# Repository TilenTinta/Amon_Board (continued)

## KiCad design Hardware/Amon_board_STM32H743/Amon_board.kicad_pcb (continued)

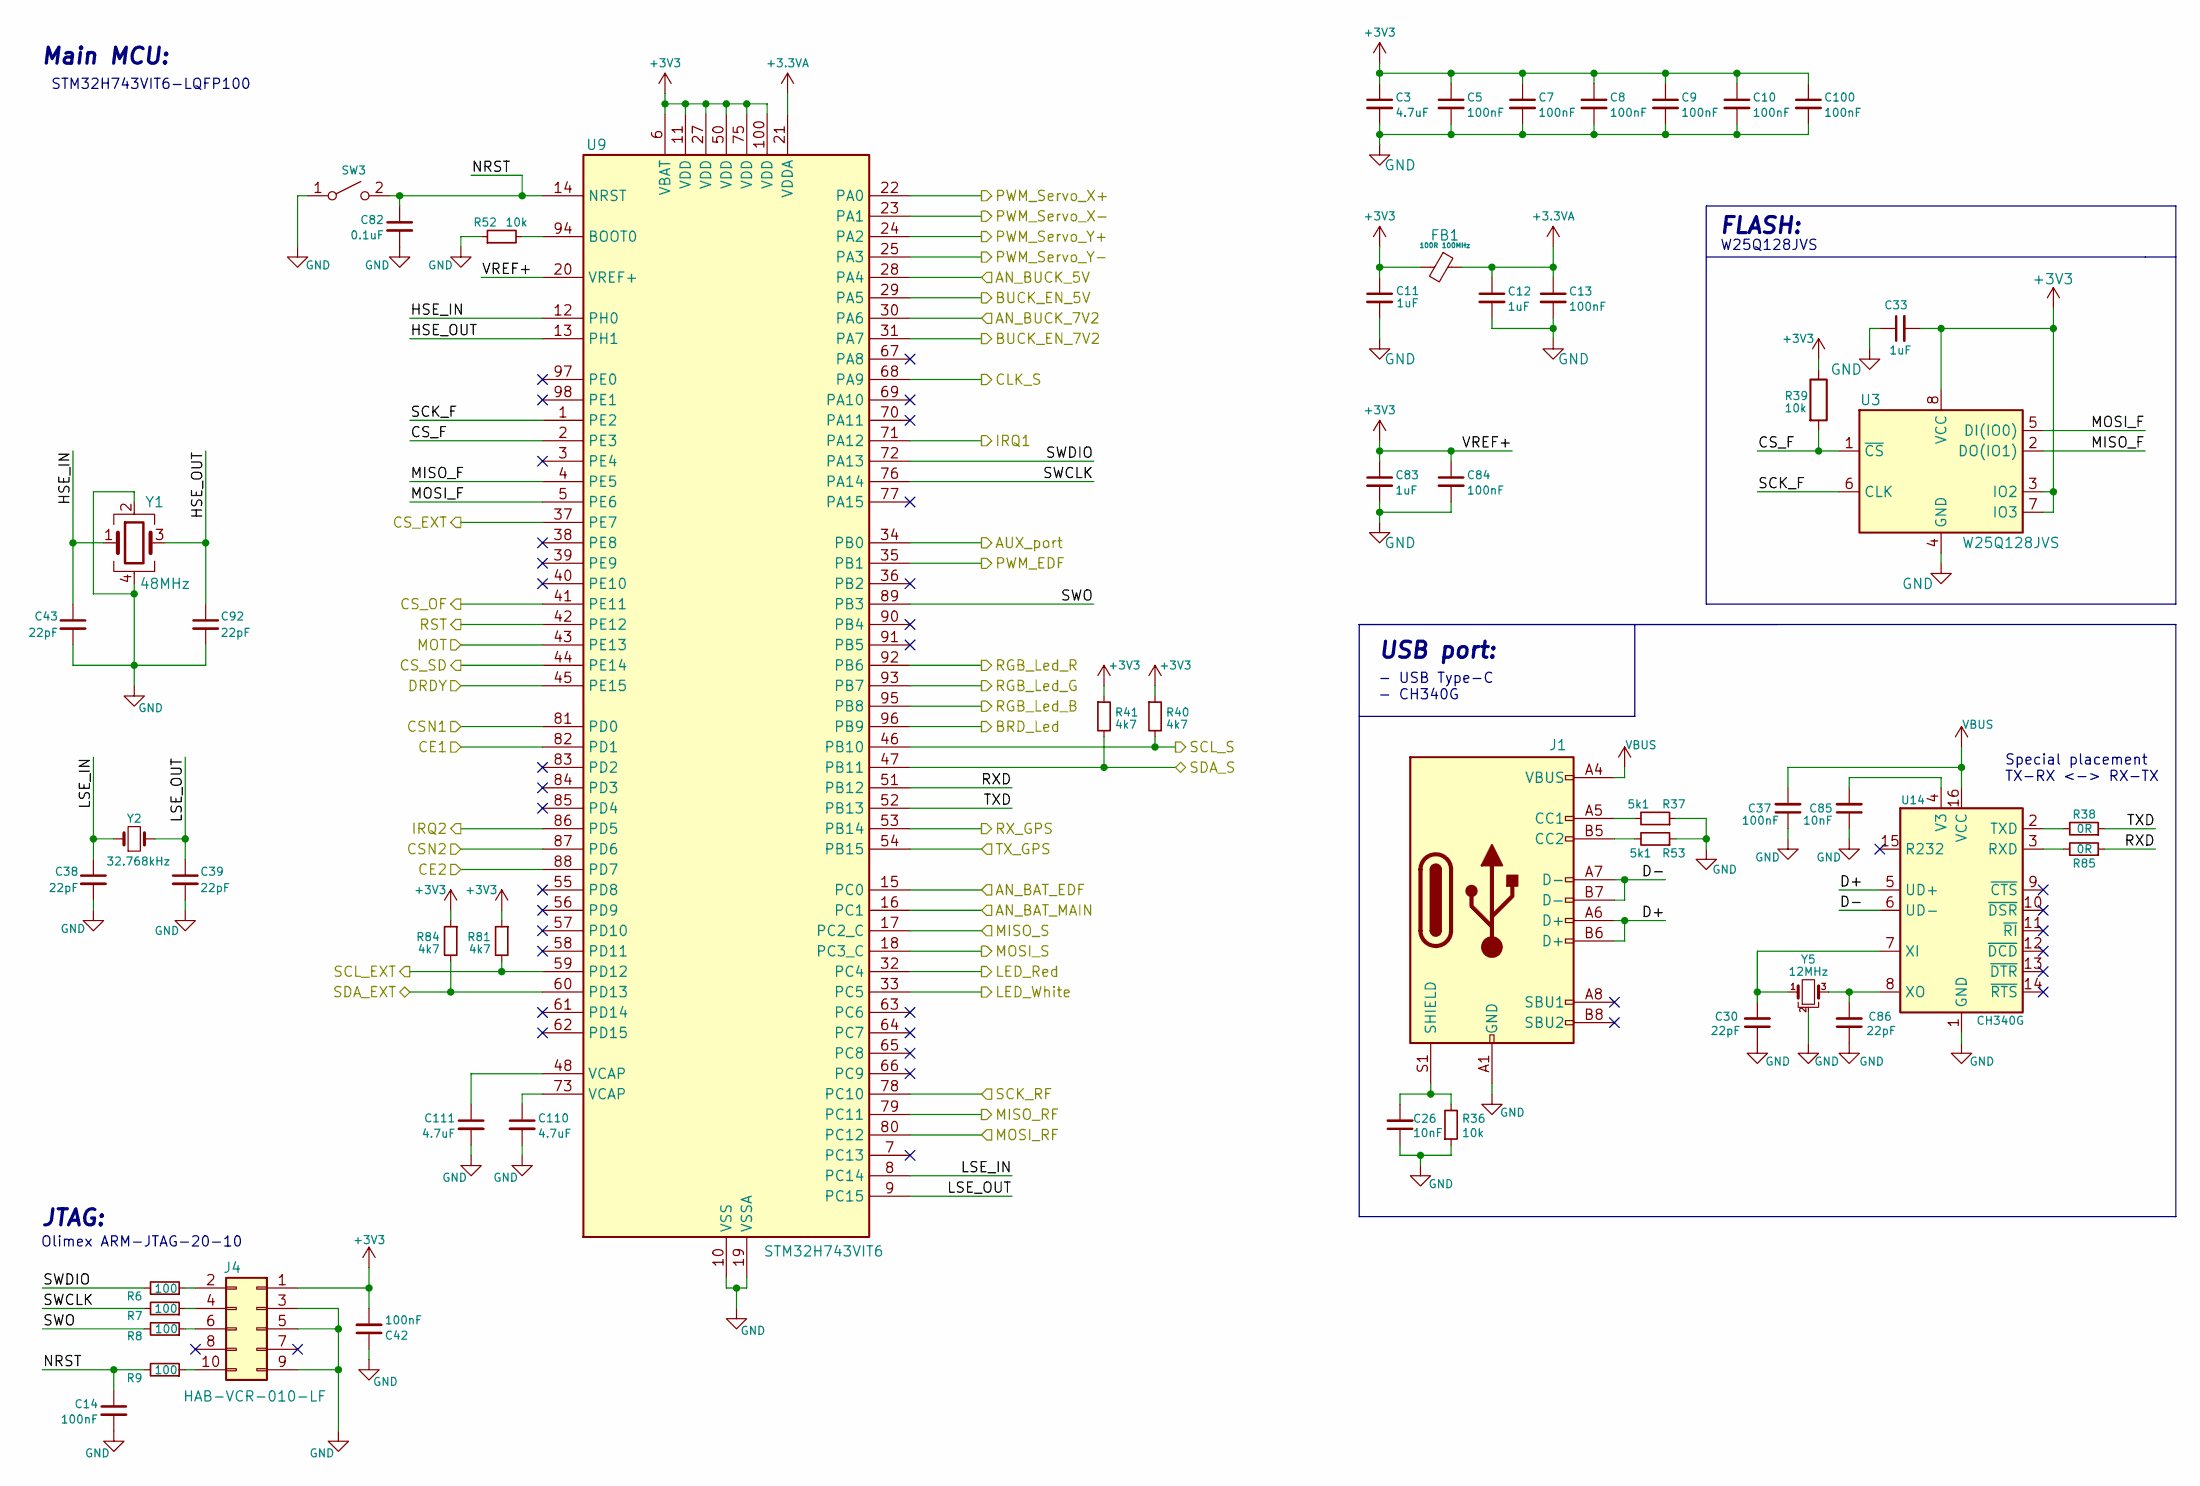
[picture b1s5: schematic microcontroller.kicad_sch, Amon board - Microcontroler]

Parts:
C3, C110, C111: 4.7uF; C_0603_1608Metric
C5, C7, C8, C9, C10, C13, C14, C37, C42, C84, C100: 100nF; C_0603_1608Metric
C11, C12, C33, C83: 1uF; C_0603_1608Metric
C26, C85: 10nF; C_0603_1608Metric
C30, C38, C39, C43, C86, C92: 22pF; C_0402_1005Metric
C82: 0.1uF; C_0603_1608Metric
FB1: 100R 100MHz; L_1206_3216Metric_Pad1.22x1.90mm_HandSolder
J1: USB_C_Receptacle_USB2.0; USB_C_Receptacle_XKB_U262-16XN-4BVC11
J4: HAB-VCR-010-LF; PinHeader_2x05_P1.27mm_Vertical_SMD
R6, R7, R8, R9: 100; R_0603_1608Metric
R36, R39, R52: 10k; R_0603_1608Metric
R37, R53: 5k1; R_0603_1608Metric
R38, R85: 0R; R_0603_1608Metric
R40, R41, R81, R84: 4k7; R_0603_1608Metric
SW3: SW_SPST; SW_Push_1P1T_NO_CK_KMR2
U3: W25Q128JVS; SOIC-8_5.23x5.23mm_P1.27mm
U9: STM32H743VIT6; LQFP-100_14x14mm_P0.5mm
U14: CH340G; SOIC-16_3.9x9.9mm_P1.27mm
Y1: 48MHz; Crystal_SMD_3225-4Pin_3.2x2.5mm
Y2: 32.768kHz; Crystal_SMD_3215-2Pin_3.2x1.5mm
Y5: 12MHz; Resonator_SMD_Murata_CSTxExxV-3Pin_3.0x1.1mm

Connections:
+3.3VA: C12.1, C13.1, FB1.1, U9.21 (VDDA)
/Devices/BRD_Led: U9.96 (PB9); also elsewhere on the board
/Devices/CLK_S: U9.68 (PA9); also elsewhere on the board
/Devices/CS_OF: U9.41 (PE11); also elsewhere on the board
/Devices/CS_SD: U9.44 (PE14); also elsewhere on the board
/Devices/DRDY: U9.45 (PE15); also elsewhere on the board
/Devices/MISO_S: U9.17 (PC2_C); also elsewhere on the board
/Devices/MOSI_S: U9.18 (PC3_C); also elsewhere on the board
/Devices/RGB_Led_B: U9.95 (PB8); also elsewhere on the board
/Devices/RGB_Led_G: U9.93 (PB7); also elsewhere on the board
/Devices/RGB_Led_R: U9.92 (PB6); also elsewhere on the board
/Microcontroller/AN_BAT_EDF: U9.15 (PC0); also elsewhere on the board
/Microcontroller/AN_BAT_MAIN: U9.16 (PC1); also elsewhere on the board
/Microcontroller/AN_BUCK_5V: U9.28 (PA4); also elsewhere on the board
/Microcontroller/AN_BUCK_7V2: U9.30 (PA6); also elsewhere on the board
/Microcontroller/AUX_port: U9.34 (PB0); also elsewhere on the board
/Microcontroller/BUCK_EN_5V: U9.29 (PA5); also elsewhere on the board
/Microcontroller/BUCK_EN_7V2: U9.31 (PA7); also elsewhere on the board
/Microcontroller/CSN1: U9.81 (PD0); also elsewhere on the board
/Microcontroller/CSN2: U9.87 (PD6); also elsewhere on the board
/Microcontroller/CS_EXT: U9.37 (PE7); also elsewhere on the board
/Microcontroller/CS_F: R39.2, U3.1 (~CS), U9.2 (PE3)
/Microcontroller/D+: J1.A6 (D+), J1.B6 (D+), U14.5 (UD+)
/Microcontroller/D-: J1.A7 (D-), J1.B7 (D-), U14.6 (UD-)
/Microcontroller/HSE_IN: C43.1, U9.12 (PH0), Y1.1
/Microcontroller/HSE_OUT: C92.1, U9.13 (PH1), Y1.3
/Microcontroller/IRQ1: U9.71 (PA12); also elsewhere on the board
/Microcontroller/IRQ2: U9.86 (PD5); also elsewhere on the board
/Microcontroller/LED_Red: U9.32 (PC4); also elsewhere on the board
/Microcontroller/LED_White: U9.33 (PC5); also elsewhere on the board
/Microcontroller/LSE_IN: C38.1, U9.8 (PC14), Y2.1
/Microcontroller/LSE_OUT: C39.1, U9.9 (PC15), Y2.2
/Microcontroller/MISO_F: U3.2 (DO(IO1)), U9.4 (PE5)
/Microcontroller/MISO_RF: U9.79 (PC11); also elsewhere on the board
/Microcontroller/MOSI_F: U3.5 (DI(IO0)), U9.5 (PE6)
/Microcontroller/MOSI_RF: U9.80 (PC12); also elsewhere on the board
/Microcontroller/NRST: C14.1, C82.1, R9.2, SW3.2 (B), U9.14 (NRST)
/Microcontroller/PWM_EDF: U9.35 (PB1); also elsewhere on the board
/Microcontroller/PWM_Servo_X+: U9.22 (PA0); also elsewhere on the board
/Microcontroller/PWM_Servo_X-: U9.23 (PA1); also elsewhere on the board
/Microcontroller/PWM_Servo_Y+: U9.24 (PA2); also elsewhere on the board
/Microcontroller/PWM_Servo_Y-: U9.25 (PA3); also elsewhere on the board
/Microcontroller/RXD: R85.1, U9.51 (PB12)
/Microcontroller/RX_GPS: U9.53 (PB14); also elsewhere on the board
/Microcontroller/SCK_F: U3.6 (CLK), U9.1 (PE2)
/Microcontroller/SCK_RF: U9.78 (PC10); also elsewhere on the board
/Microcontroller/SCL_EXT: R81.2, U9.59 (PD12); also elsewhere on the board
/Microcontroller/SDA_EXT: R84.2, U9.60 (PD13); also elsewhere on the board
/Microcontroller/SWCLK: R7.2, U9.76 (PA14)
/Microcontroller/SWDIO: R6.2, U9.72 (PA13)
/Microcontroller/SWO: R8.2, U9.89 (PB3)
/Microcontroller/TXD: R38.1, U9.52 (PB13)
/Microcontroller/TX_GPS: U9.54 (PB15); also elsewhere on the board
/RF/CE1: U9.82 (PD1); also elsewhere on the board
/RF/CE2: U9.88 (PD7); also elsewhere on the board
unnamed: C110.1, U9.73 (VCAP)
unnamed: C111.1, U9.48 (VCAP)
unnamed: J1.A5 (CC1), R37.2
unnamed: J1.B5 (CC2), R53.2
unnamed: C26.2, J1.S1 (SHIELD), R36.2
unnamed: J4.2, R6.1
unnamed: J4.4, R7.1
unnamed: J4.6, R8.1
unnamed: J4.10, R9.1
unnamed: R52.2, U9.94 (BOOT0)
unnamed: R85.2, U14.3 (RXD)
unnamed: R38.2, U14.2 (TXD)
unnamed: C85.2, U14.4 (V3)
unnamed: C30.2, U14.7 (XI), Y5.1
unnamed: C86.2, U14.8 (XO), Y5.3
VBUS: C37.2, J1.A4 (VBUS), J1.A9 (VBUS), J1.B4 (VBUS), J1.B9 (VBUS), U14.16 (VCC)

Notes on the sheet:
- USB Type-C - CH340G
USB port:
Main MCU:
JTAG:
Olimex ARM-JTAG-20-10
W25Q128JVS
STM32H743VIT6-LQFP100
FLASH:
Special placement TX-RX <-> RX-TX

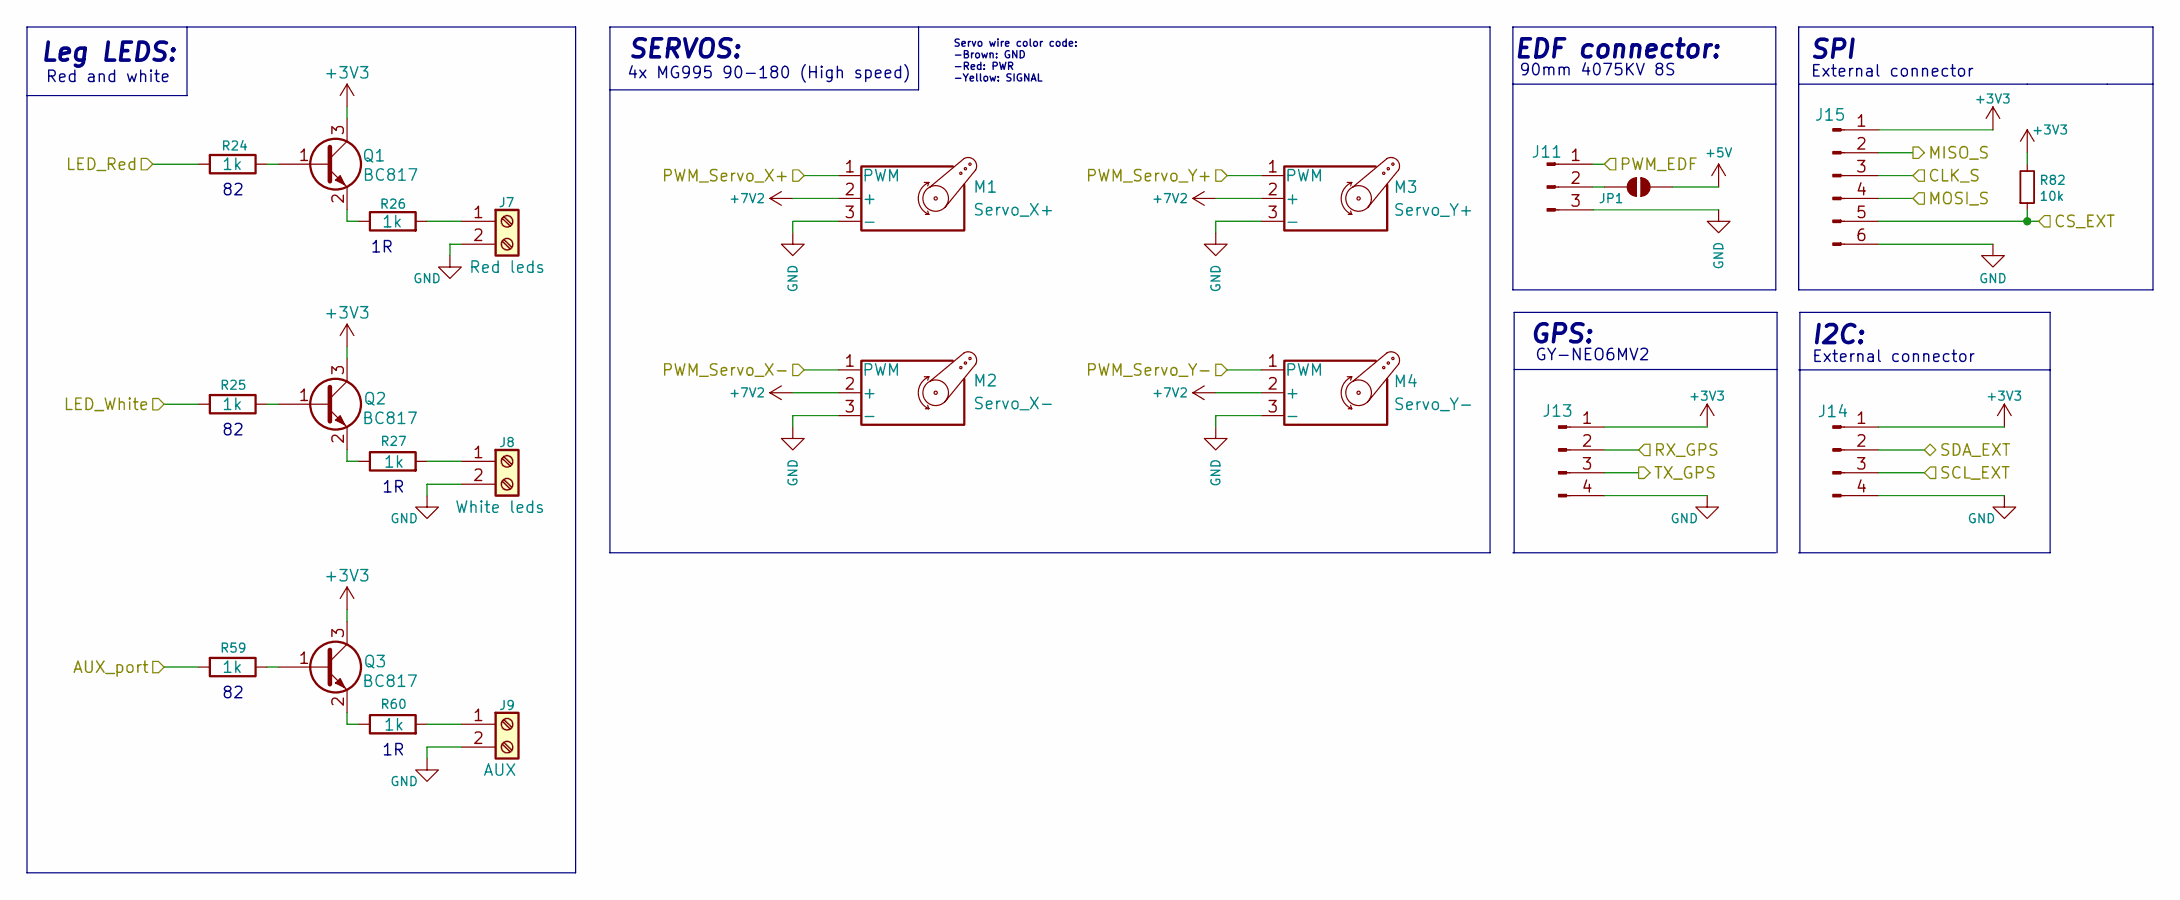
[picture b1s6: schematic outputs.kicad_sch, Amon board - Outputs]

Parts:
J7: Red leds; TerminalBlock_MetzConnect_Type059_RT06302HBWC_1x02_P3.50mm_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
J8: White leds; TerminalBlock_MetzConnect_Type059_RT06302HBWC_1x02_P3.50mm_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
J9: AUX; TerminalBlock_MetzConnect_Type059_RT06302HBWC_1x02_P3.50mm_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
J11: Conn_01x03_Male; PinHeader_1x03_P2.54mm_Vertical
J13: Conn_01x04_Male; JST_XH_S4B-XH-A_1x04_P2.50mm_Horizontal
J14: Conn_01x04_Male; PinHeader_1x04_P2.54mm_Vertical
J15: Conn_01x06_Male; PinHeader_1x06_P2.54mm_Vertical
JP1: SolderJumper_2_Open; SolderJumper-2_P1.3mm_Open_RoundedPad1.0x1.5mm
M1: Servo_X+; PinHeader_1x03_P2.54mm_Vertical
M2: Servo_X-; PinHeader_1x03_P2.54mm_Vertical
M3: Servo_Y+; PinHeader_1x03_P2.54mm_Vertical
M4: Servo_Y-; PinHeader_1x03_P2.54mm_Vertical
Q1, Q2, Q3: BC817; SOT-23
R24, R25, R26, R27, R59, R60: 1k; R_0603_1608Metric
R82: 10k; R_0603_1608Metric

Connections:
+5V: JP1.2 (B); also elsewhere on the board
+7V2: M1.2 (+), M2.2 (+), M3.2 (+), M4.2 (+); also elsewhere on the board
/Devices/CLK_S: J15.3; also elsewhere on the board
/Devices/MISO_S: J15.2; also elsewhere on the board
/Devices/MOSI_S: J15.4; also elsewhere on the board
/Microcontroller/AUX_port: R59.2; also elsewhere on the board
/Microcontroller/CS_EXT: J15.5, R82.1; also elsewhere on the board
/Microcontroller/LED_Red: R24.2; also elsewhere on the board
/Microcontroller/LED_White: R25.2; also elsewhere on the board
/Microcontroller/PWM_EDF: J11.1; also elsewhere on the board
/Microcontroller/PWM_Servo_X+: M1.1 (PWM); also elsewhere on the board
/Microcontroller/PWM_Servo_X-: M2.1 (PWM); also elsewhere on the board
/Microcontroller/PWM_Servo_Y+: M3.1 (PWM); also elsewhere on the board
/Microcontroller/PWM_Servo_Y-: M4.1 (PWM); also elsewhere on the board
/Microcontroller/RX_GPS: J13.2; also elsewhere on the board
/Microcontroller/SCL_EXT: J14.3; also elsewhere on the board
/Microcontroller/SDA_EXT: J14.2; also elsewhere on the board
/Microcontroller/TX_GPS: J13.3; also elsewhere on the board
unnamed: J7.1, R26.2
unnamed: J8.1, R27.2
unnamed: J9.1, R60.2
unnamed: J11.2, JP1.1 (A)
unnamed: Q1.1 (B), R24.1
unnamed: Q1.2 (E), R26.1
unnamed: Q2.1 (B), R25.1
unnamed: Q2.2 (E), R27.1
unnamed: Q3.1 (B), R59.1
unnamed: Q3.2 (E), R60.1

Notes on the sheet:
SPI
90mm 4075KV 8S
4x MG995 90-180 (High speed)
External connector
Red and white
EDF connector:
Leg LEDS:
SERVOS:
Servo wire color code: -Brown: GND -Red: PWR -Yellow: SIGNAL
GPS:
I2C:
GY-NEO6MV2

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
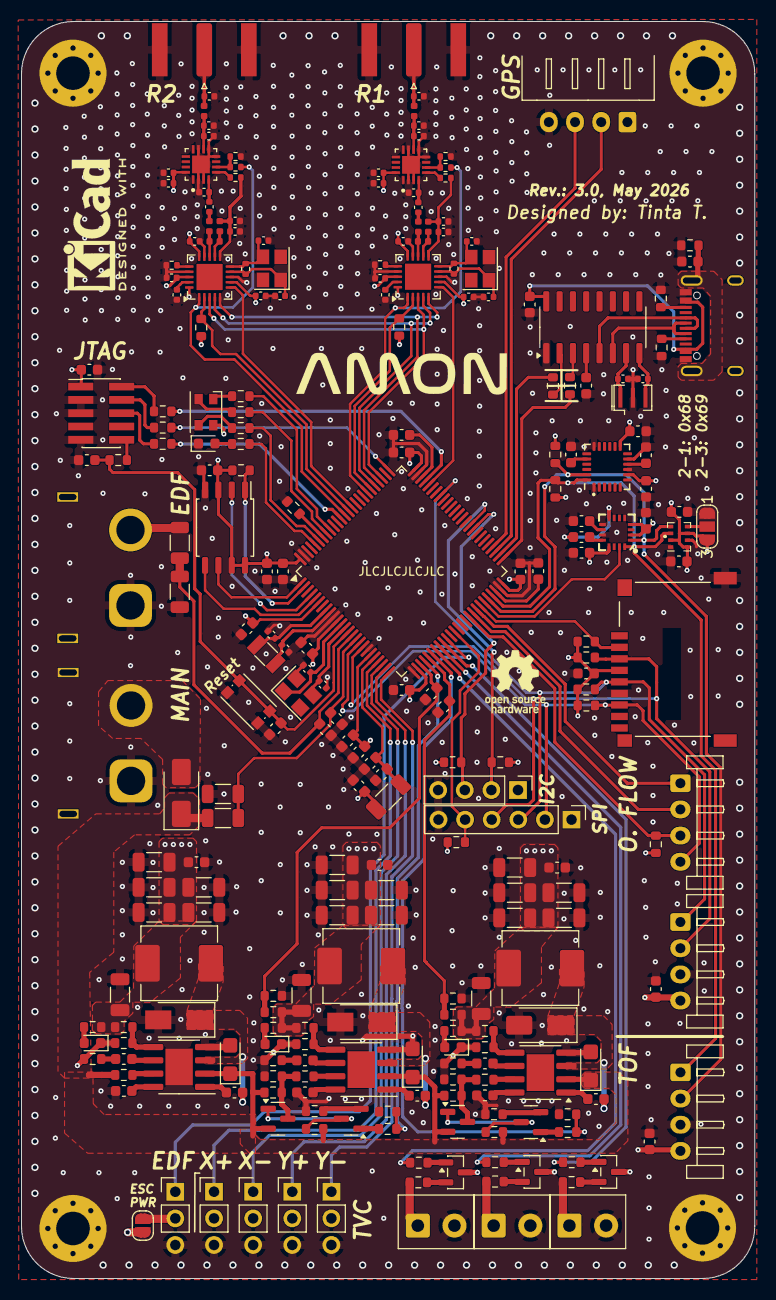
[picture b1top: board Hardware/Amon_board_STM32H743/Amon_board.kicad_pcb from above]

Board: 4 copper layers, 70.0 x 120.0 mm, 259 parts (0 on the bottom side), 160 nets.

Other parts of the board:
J18, J19: SMA Edge; SMA_Amphenol_132289_EdgeMount
R61, R62: 10k; R_0603_1608Metric

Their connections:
/Microcontroller/CSN1: R61.2; also elsewhere on the board
/Microcontroller/CSN2: R62.2; also elsewhere on the board

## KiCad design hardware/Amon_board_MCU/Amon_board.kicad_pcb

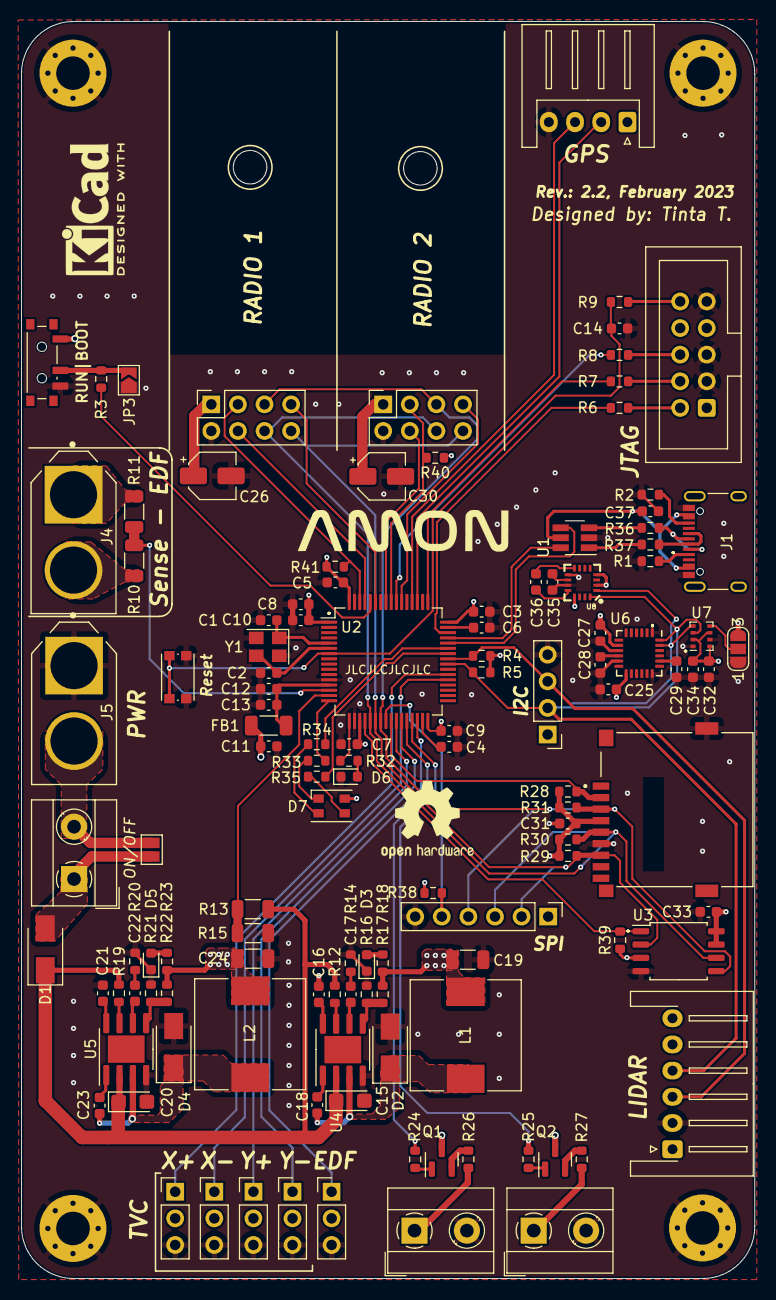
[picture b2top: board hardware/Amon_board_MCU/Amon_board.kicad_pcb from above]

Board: 4 copper layers, 70.0 x 120.0 mm, 129 parts (0 on the bottom side), 93 nets.

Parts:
C1, C2: 14pF; C_0603_1608Metric
C3, C35: 4.7uF; C_0603_1608Metric
C4, C6: 2.2uF; C_0603_1608Metric
C5, C7, C8, C9, C10, C13, C14, C16, C21, C32, C34, C37: 100nF; C_0603_1608Metric
C11, C12, C33: 1uF; C_0603_1608Metric
C15, C20: 10uF; CP_EIA-3216-10_Kemet-I
C17, C22: 3.9nF; C_0603_1608Metric
C18, C23: 10nF; C_0603_1608Metric
C19, C24: 22uF; C_1206_3216Metric
C25, C27, C28: 0.1uF; C_0603_1608Metric
C26, C30: 10uF; CP_Elec_4x5.4
C29: 2.2nF; C_0603_1608Metric
C31: 10uF; C_0603_1608Metric
C36: 0.22uF; C_0603_1608Metric
D1, D2, D4: B120-E3; D_SMA
D3, D5: Red; LED_0603_1608Metric
D6: RED; LED_0603_1608Metric
D7: LED_RGBA; LED_Cree-PLCC4_3.2x2.8mm_CCW
FB1: 100R 100MHz; L_1206_3216Metric_Pad1.22x1.90mm_HandSolder
H1, H2, H3, H4: MountingHole_Pad; MountingHole_3.2mm_M3_Pad_Via
H5, H6: MountingHole; MountingHole_3.2mm_M3
J1: USB2.0_C_Rev; USB_C_Receptacle_XKB_U262-16XN-4BVC11
J2: Conn_2x5 pin; IDC-Header_2x05_P2.54mm_Vertical
J3: Switch_port; TerminalBlock_MetzConnect_Type055_RT01502HDWU_1x02_P5.00mm_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
J4, J5: XT60-F; AMASS_XT60-M
J6, J9: Conn_02x04_Odd_Even; PinSocket_2x04_P2.54mm_Vertical
J7: Red leds; TerminalBlock_MetzConnect_Type055_RT01502HDWU_1x02_P5.00mm_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
J8: White leds; TerminalBlock_MetzConnect_Type055_RT01502HDWU_1x02_P5.00mm_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
J10: GTFP08131Y2HR; AMPHENOL_GTFP08131Y2HR
J11: Conn_01x03_Male; PinHeader_1x03_P2.54mm_Vertical
J12: Conn_01x06_Male; JST_XH_S6B-XH-A-1_1x06_P2.50mm_Horizontal
J13: Conn_01x04_Male; JST_XH_S4B-XH-A_1x04_P2.50mm_Horizontal
J14: Conn_01x04_Male; PinHeader_1x04_P2.54mm_Vertical
J15: Conn_01x06_Male; PinHeader_1x06_P2.54mm_Vertical
JP1: SolderJumper_2_Open; SolderJumper-2_P1.3mm_Open_Pad1.0x1.5mm
JP2: I2C address; SolderJumper-3_P1.3mm_Open_RoundedPad1.0x1.5mm_NumberLabels
JP3: SolderJumper_2_Open; SolderJumper-2_P1.3mm_Open_TrianglePad1.0x1.5mm
L1, L2: 10uH 4A; L_10.4x10.4_H4.8
M1: Servo_X+; PinHeader_1x03_P2.54mm_Vertical
M2: Servo_X-; PinHeader_1x03_P2.54mm_Vertical
M3: Servo_Y+; PinHeader_1x03_P2.54mm_Vertical
M4: Servo_Y-; PinHeader_1x03_P2.54mm_Vertical
Q1, Q2: BC817; SOT-23
R1, R2: 5k1; R_0603_1608Metric
R3, R16, R21, R28, R29, R30, R31, R38, R39, R40, R41: 10k; R_0603_1608Metric
R4, R5: 4k7; R_0603_1608Metric
R6, R7, R8, R9: 100; R_0603_1608Metric
R10, R13: 100k; R_1206_3216Metric
R11, R15: 10k; R_1206_3216Metric
R12, R19: 100k; R_0603_1608Metric
R14, R20: 6k8; R_0603_1608Metric
R17: 26k1; R_0603_1608Metric
R18, R23: 1k5; R_0603_1608Metric
R22: 44k; R_0603_1608Metric
R24, R25, R26, R27: 1k; R_0603_1608Metric
R32, R33, R34, R35: 330; R_0603_1608Metric
R36, R37: 22; R_0603_1608Metric
SW1: SW_DPDT; SW_SPDT_PCM12
SW2: SW_SPST; SW_Push_1P1T_NO_CK_KMR2
U1: USBLC6-2P6; SOT-23-6_Handsoldering
U2: STM32F405RGT6-LQFP64; LQFP-64_10x10mm_P0.5mm
U3: W25Q128JVS; SOIC-8_5.23x5.23mm_P1.27mm
U4, U5: MP2303ADN; SOIC-8-1EP_3.9x4.9mm_P1.27mm_EP2.62x3.51mm
U6: MPU-6050; InvenSense_QFN-24_4x4mm_P0.5mm
U7: BME280; Bosch_LGA-8_2x2.5mm_P0.65mm_ClockwisePinNumbering
U8: HMC5883L; LPCC-16
Y1: 25MHz; Crystal_SMD_3225-4Pin_3.2x2.5mm

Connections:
+3.3VA: C12.1, C13.1, FB1.1, U2.13 (VDDA)
+3V3: C3.1, C5.1, C7.1, C8.1, C9.1, C10.1, C11.1, C19.2, C25.1, C26.1, C27.1, C30.1, C31.2, C32.1, C33.2, C34.2, D7.4 (A), FB1.2, J2.1, J6.1, J9.1, J10.4 (VDD), J12.1, J13.1, J14.1, J15.1, JP2.3 (B), L1.2, Q1.3 (C), Q2.3 (C), R4.1, R5.1, R17.2, R18.1, R28.1, R29.1, R30.1, R31.1, R38.1, R39.1, R40.1, R41.1, SW1.1 (A), U2.1 (VBAT), U2.19 (VDD), U2.32 (VDD), U2.48 (VDD), U2.64 (VDD), U3.3 (IO2), U3.7 (IO3), U3.8 (VCC), U6.8 (VDDIO), U6.13 (VDD), U7.2 (CSB), U7.6 (VDDIO), U7.8 (VDD), U8.2 (VDD), U8.4 (S1), U8.13 (VDDIO)
+5V: C24.2, J11.2, L2.2, M1.2 (+), M2.2 (+), M3.2 (+), M4.2 (+), R22.2, R23.1
/HSE_IN: C1.1, U2.5 (PH0), Y1.1
/HSE_OUT: C2.1, U2.6 (PH1), Y1.3
/IN_D+: R37.2, U1.1 (I/O1)
/IN_D-: R36.2, U1.3 (I/O2)
/NRST: C14.1, R9.2, SW2.2 (B), U2.7 (NRST)
/Power/12V: C15.1, C20.1, D1.1 (K), R12.1, R13.1, R19.1, U4.2 (IN), U5.2 (IN)
/Power/VBAT+: J3.2, J5.2 (+), JP1.2 (B)
/SWDCLK: R7.2, U2.49 (PA14)
/SWDIO: R6.2, U2.46 (PA13)
/SWO: R8.2, U2.55 (PB3)
/USB_D+: U1.6 (I/O1), U2.45 (PA12)
/USB_D-: U1.4 (I/O2), U2.44 (PA11)
BAT_BRD_S: R13.2, R15.1, U2.15 (PA1)
BAT_EDF_S: R10.2, R11.1, U2.14 (PA0)
Brd_Led: R32.1, U2.17 (PA3)
CLK: J6.6, J9.6, J10.5 (CLK), J15.3, R30.2, U2.21 (PA5), U3.6 (CLK)
CS_EXT: J15.5, R38.2, U2.24 (PC4)
CS_Flash: R39.2, U2.20 (PA4), U3.1 (~CS)
CS_RF1: J6.3, R41.2, U2.62 (PB9)
CS_RF2: J9.3, R40.2, U2.56 (PB4)
CS_SD: J10.2 (CD/DAT3), R28.2, U2.25 (PC5)
EN_RF1: J6.4, U2.61 (PB8)
EN_RF2: J9.4, U2.57 (PB5)
GND: C1.2, C2.2, C3.2, C4.2, C5.2, C6.2, C7.2, C8.2, C9.2, C10.2, C11.2, C12.2, C13.2, C14.2, C15.2, C16.2, C19.1, C20.2, C21.2, C24.1, C25.2, C26.2, C27.2, C28.2, C29.2, C30.2, C31.1, C32.2, C33.1, C34.1, C35.1, C37.2, D2.2 (A), D3.1 (K), D4.2 (A), D5.1 (K), D6.1 (K), H1.1, H2.1, H3.1, H4.1, J1.A1 (GND), J1.A12 (GND), J1.B1 (GND), J1.B12 (GND), J2.3, J2.5, J2.9, J5.1 (-), J6.2, J7.2, J8.2, J9.2, J10.6 (VSS), J10.S4 (SHIELD_GND), J11.3, J12.2, J13.4, J14.4, J15.6, JP2.1 (A), JP3.1 (A), M1.3 (-), M2.3 (-), M3.3 (-), M4.3 (-), R1.2, R2.2, R14.1, R15.2, R16.1, R20.1, R21.1, SW1.3 (C), SW2.1 (A), U1.2 (GND), U2.12 (VSSA), U2.18 (VSS), U2.63 (VSS), U3.4 (GND), U4.4 (GND), U5.4 (GND), U6.1 (CLKIN), U6.9 (AD0), U6.11 (FSYNC), U6.18 (GND), U7.1 (GND), U7.7 (GND), U8.9 (GND@1), U8.11 (GND@2), Y1.2, Y1.4
GND1: J4.1 (-), R11.2
LED_Red: R24.2, U2.28 (PB2)
LED_White: R25.2, U2.29 (PB10)
MISO: J6.8, J9.8, J10.7 (DAT0), J15.2, R29.2, U2.22 (PA6), U3.2 (DO(IO1))
MOSI: J6.5, J9.5, J10.3 (CMD), J15.4, R31.2, U2.23 (PA7), U3.5 (DI(IO0))
unnamed: C17.2, R14.2
unnamed: C22.2, R20.2
unnamed: D1.2 (A), J3.1, JP1.1 (A)
unnamed: C18.2, D2.1 (K), L1.1, U4.3 (SW)
unnamed: D3.2 (A), R18.2
unnamed: C23.2, D4.1 (K), L2.1, U5.3 (SW)
unnamed: D5.2 (A), R23.2
unnamed: D6.2 (A), R32.2
unnamed: D7.3 (BK), R35.2
unnamed: D7.2 (GK), R34.2
unnamed: D7.1 (RK), R33.2
unnamed: J1.A5 (CC1), R1.1
unnamed: J1.B5 (CC2), R2.1
unnamed: J1.A6 (D+), J1.B6 (D+), R37.1
unnamed: J1.A7 (D-), J1.B7 (D-), R36.1
unnamed: J2.2, R6.1
unnamed: J2.4, R7.1
unnamed: J2.6, R8.1
unnamed: J2.10, R9.1
unnamed: J4.2 (+), R10.1
unnamed: J7.1, R26.2
unnamed: J8.1, R27.2
unnamed: JP2.2 (C), U7.5 (SDO)
unnamed: JP3.2 (B), R3.1, SW1.2 (B)
unnamed: Q1.1 (B), R24.1
unnamed: Q1.2 (E), R26.1
unnamed: Q2.1 (B), R25.1
unnamed: Q2.2 (E), R27.1
unnamed: R3.2, U2.60 (BOOT0)
unnamed: C4.1, U2.31 (VCAP_1)
unnamed: C6.1, U2.47 (VCAP_2)
unnamed: C18.1, U4.1 (BS)
unnamed: C17.1, U4.6 (COMP)
unnamed: R12.2, U4.7 (EN)
unnamed: R16.2, R17.1, U4.5 (FB)
unnamed: C16.1, U4.8 (SS)
unnamed: C23.1, U5.1 (BS)
unnamed: C22.1, U5.6 (COMP)
unnamed: R19.2, U5.7 (EN)
unnamed: R21.2, R22.1, U5.5 (FB)
unnamed: C21.1, U5.8 (SS)
unnamed: C29.1, U6.20 (CPOUT)
unnamed: C28.1, U6.10 (REGOUT)
unnamed: C35.2, U8.10 (C1)
unnamed: C36.1, U8.12 (SETC)
unnamed: C36.2, U8.8 (SETP)
PWM_EDF: J11.1, U2.30 (PB11)
PWM_Servo_X+: M1.1 (PWM), U2.38 (PC7)
PWM_Servo_X-: M2.1 (PWM), U2.37 (PC6)
PWM_Servo_Y+: M3.1 (PWM), U2.26 (PB0)
PWM_Servo_Y-: M4.1 (PWM), U2.27 (PB1)
RF_IRQ1: J6.7, U2.59 (PB7)
RF_IRQ2: J9.7, U2.54 (PD2)
RGB_Led_B: R35.1, U2.42 (PA9)
RGB_Led_G: R34.1, U2.43 (PA10)
RGB_Led_R: R33.1, U2.16 (PA2)
RX_GPS: J13.3, U2.52 (PC11)
SCL: J12.3, J14.3, R4.2, U2.41 (PA8), U6.23 (SCL), U7.4 (SCK), U8.1 (SCL)
SDA: J12.4, J14.2, R5.2, U2.40 (PC9), U6.24 (SDA), U7.3 (SDI), U8.16 (SDA)
TX_GPS: J13.2, U2.51 (PC10)
VBUS: C37.1, J1.A4 (VBUS), J1.A9 (VBUS), J1.B4 (VBUS), J1.B9 (VBUS), U1.5 (VBUS)

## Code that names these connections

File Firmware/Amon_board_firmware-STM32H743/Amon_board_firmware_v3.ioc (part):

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Mcu.Name=STM32H743VITx
Mcu.Package=LQFP100
Mcu.UserName=STM32H743VITx
PA0.GPIOParameters=GPIO_PuPd,GPIO_Label
PA0.GPIO_Label=SERVO_XP
PA0.GPIO_PuPd=GPIO_PULLDOWN
PA0.Signal=S_TIM2_CH1_ETR
PA1.GPIOParameters=GPIO_PuPd,GPIO_Label
PA1.GPIO_Label=SERVO_XN
PA1.GPIO_PuPd=GPIO_PULLDOWN
PA1.Signal=S_TIM2_CH2
PA12.GPIOParameters=GPIO_PuPd,GPIO_Label,GPIO_ModeDefaultEXTI
PA12.GPIO_Label=RF1_IRQ
PA12.GPIO_ModeDefaultEXTI=GPIO_MODE_IT_FALLING
PA12.GPIO_PuPd=GPIO_NOPULL
PA12.Signal=GPXTI12
PA13\ (JTMS/SWDIO).Mode=Trace_Asynchronous_SW
PA13\ (JTMS/SWDIO).Signal=DEBUG_JTMS-SWDIO
PA14\ (JTCK/SWCLK).Mode=Trace_Asynchronous_SW
PA14\ (JTCK/SWCLK).Signal=DEBUG_JTCK-SWCLK
PA2.GPIOParameters=GPIO_PuPd,GPIO_Label
PA2.GPIO_Label=SERVO_YP
PA2.GPIO_PuPd=GPIO_PULLDOWN
PA2.Signal=S_TIM2_CH3
PA3.GPIOParameters=GPIO_PuPd,GPIO_Label
PA3.GPIO_Label=SERVO_YN
PA3.GPIO_PuPd=GPIO_PULLDOWN
PA3.Signal=S_TIM2_CH4
PA4.GPIOParameters=GPIO_Label
PA4.GPIO_Label=ADC1_18_BUCK_5V
PA4.Signal=ADCx_INP18
PA5.GPIOParameters=GPIO_Label
PA5.GPIO_Label=EN_BUCK_5V
PA5.Signal=GPIO_Output
PA6.GPIOParameters=GPIO_Label
PA6.GPIO_Label=ADC1_3_BUCK_7V2
PA6.Signal=ADCx_INP3
PA7.GPIOParameters=GPIO_Label
PA7.GPIO_Label=EN_BUCK_7V2
PA7.Signal=GPIO_Output
PA9.GPIOParameters=GPIO_Speed
PA9.GPIO_Speed=GPIO_SPEED_FREQ_VERY_HIGH
PA9.Mode=Full_Duplex_Master
PA9.Signal=SPI2_SCK
PB0.GPIOParameters=GPIO_Label
PB0.GPIO_Label=AUX_PORT
PB0.Signal=GPIO_Output
PB1.GPIOParameters=GPIO_PuPd,GPIO_Label
PB1.GPIO_Label=EDF
PB1.GPIO_PuPd=GPIO_PULLDOWN
PB1.Signal=S_TIM3_CH4
PB10.GPIOParameters=GPIO_Label
PB10.GPIO_Label=I2C_SCL_S
PB10.Mode=I2C
PB10.Signal=I2C2_SCL
PB11.GPIOParameters=GPIO_Label
PB11.GPIO_Label=I2C_SDA_S
PB11.Mode=I2C
PB11.Signal=I2C2_SDA
PB12.GPIOParameters=GPIO_Label
PB12.GPIO_Label=UART5_RX_USB
PB12.Mode=Asynchronous
PB12.Signal=UART5_RX
PB13.GPIOParameters=GPIO_Label
PB13.GPIO_Label=UART5_TX_USB
PB13.Mode=Asynchronous
PB13.Signal=UART5_TX
PB14.GPIOParameters=GPIO_Label
PB14.GPIO_Label=UART1_TX_GPS
PB14.Mode=Asynchronous
PB14.Signal=USART1_TX
PB15.GPIOParameters=GPIO_Label
PB15.GPIO_Label=UART1_RX_GPS
PB15.Mode=Asynchronous
PB15.Signal=USART1_RX
PB3\ (JTDO/TRACESWO).Mode=Trace_Asynchronous_SW
PB3\ (JTDO/TRACESWO).Signal=DEBUG_JTDO-SWO
PB6.GPIOParameters=GPIO_Label
PB6.GPIO_Label=RGB_R
PB6.Signal=S_TIM4_CH1
PB7.GPIOParameters=GPIO_Label
PB7.GPIO_Label=RGB_G
PB7.Signal=S_TIM4_CH2
PB8.GPIOParameters=GPIO_Label
PB8.GPIO_Label=RGB_B
PB8.Signal=S_TIM4_CH3
PB9.GPIOParameters=GPIO_Speed,GPIO_Label
PB9.GPIO_Label=LED_BRD
PB9.GPIO_Speed=GPIO_SPEED_FREQ_MEDIUM
PB9.Signal=GPIO_Output
PC0.GPIOParameters=GPIO_Label
PC0.GPIO_Label=ADC1_10_EDF
PC0.Signal=ADCx_INP10
PC1.GPIOParameters=GPIO_Label
PC1.GPIO_Label=ADC1_11_MAIN
PC1.Signal=ADCx_INP11
PC10.GPIOParameters=GPIO_Speed,GPIO_Label
PC10.GPIO_Label=SPI3_SCK_RF
PC10.GPIO_Speed=GPIO_SPEED_FREQ_VERY_HIGH
PC10.Mode=Full_Duplex_Master
PC10.Signal=SPI3_SCK
PC11.GPIOParameters=GPIO_Speed,GPIO_Label
PC11.GPIO_Label=SPI3_MISO_RF
PC11.GPIO_Speed=GPIO_SPEED_FREQ_VERY_HIGH
PC11.Mode=Full_Duplex_Master
PC11.Signal=SPI3_MISO
PC12.GPIOParameters=GPIO_Speed,GPIO_Label
PC12.GPIO_Label=SPI3_MOSI_RF
PC12.GPIO_Speed=GPIO_SPEED_FREQ_VERY_HIGH
PC12.Mode=Full_Duplex_Master
PC12.Signal=SPI3_MOSI
PC14-OSC32_IN\ (OSC32_IN).Mode=LSE-External-Oscillator
PC14-OSC32_IN\ (OSC32_IN).Signal=RCC_OSC32_IN
PC15-OSC32_OUT\ (OSC32_OUT).Mode=LSE-External-Oscillator
PC15-OSC32_OUT\ (OSC32_OUT).Signal=RCC_OSC32_OUT
PC2_C.GPIOParameters=GPIO_Speed
PC2_C.GPIO_Speed=GPIO_SPEED_FREQ_VERY_HIGH
PC2_C.Mode=Full_Duplex_Master
PC2_C.Signal=SPI2_MISO
PC3_C.GPIOParameters=GPIO_Speed
PC3_C.GPIO_Speed=GPIO_SPEED_FREQ_VERY_HIGH
PC3_C.Mode=Full_Duplex_Master
PC3_C.Signal=SPI2_MOSI
PC4.GPIOParameters=GPIO_Label
PC4.GPIO_Label=LED_RED
PC4.Signal=GPIO_Output
PC5.GPIOParameters=GPIO_Label
PC5.GPIO_Label=LED_WHITE
PC5.Signal=GPIO_Output
PD0.GPIOParameters=GPIO_Speed,PinState,GPIO_Label
PD0.GPIO_Label=RF1_CSN
PD0.GPIO_Speed=GPIO_SPEED_FREQ_VERY_HIGH
PD0.PinState=GPIO_PIN_SET
PD0.Signal=GPIO_Output
PD1.GPIOParameters=GPIO_Speed,GPIO_Label
PD1.GPIO_Label=RF1_CE
PD1.GPIO_Speed=GPIO_SPEED_FREQ_VERY_HIGH
PD1.Signal=GPIO_Output
PD12.GPIOParameters=GPIO_Label
PD12.GPIO_Label=I2C_SCL_EXT
PD12.Mode=I2C
PD12.Signal=I2C4_SCL
PD13.GPIOParameters=GPIO_Label
PD13.GPIO_Label=I2C_SDA_EXT
PD13.Mode=I2C
PD13.Signal=I2C4_SDA
PD5.GPIOParameters=GPIO_PuPd,GPIO_Label,GPIO_ModeDefaultEXTI
PD5.GPIO_Label=RF2_IRQ
PD5.GPIO_ModeDefaultEXTI=GPIO_MODE_IT_FALLING
PD5.GPIO_PuPd=GPIO_NOPULL
PD5.Signal=GPXTI5
PD6.GPIOParameters=GPIO_Speed,PinState,GPIO_Label
PD6.GPIO_Label=RF2_CSN
PD6.GPIO_Speed=GPIO_SPEED_FREQ_VERY_HIGH
PD6.PinState=GPIO_PIN_SET
PD6.Signal=GPIO_Output
PD7.GPIOParameters=GPIO_Speed,GPIO_Label
PD7.GPIO_Label=RF2_CE
PD7.GPIO_Speed=GPIO_SPEED_FREQ_VERY_HIGH
PD7.Signal=GPIO_Output
PE11.GPIOParameters=GPIO_Speed,PinState,GPIO_Label
PE11.GPIO_Label=CS_OF
PE11.GPIO_Speed=GPIO_SPEED_FREQ_VERY_HIGH
PE11.PinState=GPIO_PIN_SET
PE11.Signal=GPIO_Output
PE12.GPIOParameters=PinState,GPIO_Label
PE12.GPIO_Label=OF_RST
PE12.PinState=GPIO_PIN_RESET
PE12.Signal=GPIO_Output
PE13.GPIOParameters=GPIO_Label
PE13.GPIO_Label=OF_MOT
PE13.Signal=GPXTI13
PE14.GPIOParameters=PinState,GPIO_Label
PE14.GPIO_Label=CS_SD
PE14.PinState=GPIO_PIN_SET
PE14.Signal=GPIO_Output
PE15.GPIOParameters=GPIO_Label
PE15.GPIO_Label=IRQ_DRDY
PE15.Signal=GPIO_Input
PE2.GPIOParameters=GPIO_Speed,GPIO_Label
PE2.GPIO_Label=SCK_F
PE2.GPIO_Speed=GPIO_SPEED_FREQ_VERY_HIGH
PE2.Mode=Full_Duplex_Master
PE2.Signal=SPI4_SCK
PE3.GPIOParameters=GPIO_Speed,PinState,GPIO_Label
PE3.GPIO_Label=CS_F
PE3.GPIO_Speed=GPIO_SPEED_FREQ_VERY_HIGH
PE3.PinState=GPIO_PIN_SET
PE3.Signal=GPIO_Output
PE5.GPIOParameters=GPIO_Speed,GPIO_Label
PE5.GPIO_Label=MISO_F
PE5.GPIO_Speed=GPIO_SPEED_FREQ_VERY_HIGH
PE5.Mode=Full_Duplex_Master
PE5.Signal=SPI4_MISO
PE6.GPIOParameters=GPIO_Speed,GPIO_Label
PE6.GPIO_Label=MOSI_F
PE6.GPIO_Speed=GPIO_SPEED_FREQ_VERY_HIGH
PE6.Mode=Full_Duplex_Master
PE6.Signal=SPI4_MOSI
PH0-OSC_IN\ (PH0).Mode=HSE-External-Oscillator
PH0-OSC_IN\ (PH0).Signal=RCC_OSC_IN
PH1-OSC_OUT\ (PH1).Mode=HSE-External-Oscillator
PH1-OSC_OUT\ (PH1).Signal=RCC_OSC_OUT
RCC.HSE_VALUE=48000000
RCC.SYSCLKFreq_VALUE=480000000
RCC.SYSCLKSource=RCC_SYSCLKSOURCE_PLLCLK
board=custom

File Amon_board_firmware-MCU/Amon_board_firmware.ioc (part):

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Mcu.Name=STM32F405RGTx
Mcu.Package=LQFP64
Mcu.UserName=STM32F405RGTx
PA0-WKUP.GPIOParameters=GPIO_Label
PA0-WKUP.GPIO_Label=EDF_BAT
PA0-WKUP.Signal=ADCx_IN0
PA1.GPIOParameters=GPIO_Label
PA1.GPIO_Label=BRD_BAT
PA1.Signal=ADCx_IN1
PA10.GPIOParameters=GPIO_Label
PA10.GPIO_Label=TIM1_CH3_RGB_R
PA10.Signal=S_TIM1_CH3
PA11.Mode=Device_Only
PA11.Signal=USB_OTG_FS_DM
PA12.Mode=Device_Only
PA12.Signal=USB_OTG_FS_DP
PA13.Mode=Trace_Asynchronous_SW
PA13.Signal=SYS_JTMS-SWDIO
PA14.Mode=Trace_Asynchronous_SW
PA14.Signal=SYS_JTCK-SWCLK
PA2.GPIOParameters=GPIO_Label
PA2.GPIO_Label=TIM2_CH3_RGB_B
PA2.Signal=S_TIM2_CH3
PA3.GPIOParameters=GPIO_Label
PA3.GPIO_Label=LED_Brd
PA3.Signal=GPIO_Output
PA4.GPIOParameters=GPIO_Label
PA4.GPIO_Label=CS_Flash
PA4.Signal=GPIO_Output
PA5.Mode=Full_Duplex_Master
PA5.Signal=SPI1_SCK
PA6.Mode=Full_Duplex_Master
PA6.Signal=SPI1_MISO
PA7.Mode=Full_Duplex_Master
PA7.Signal=SPI1_MOSI
PA8.Mode=I2C
PA8.Signal=I2C3_SCL
PA9.GPIOParameters=GPIO_Label
PA9.GPIO_Label=TIM1_CH2_RGB_G
PA9.Signal=S_TIM1_CH2
PB0.GPIOParameters=GPIO_Label
PB0.GPIO_Label=TIM3_CH3_Y+
PB0.Signal=S_TIM3_CH3
PB1.GPIOParameters=GPIO_Label
PB1.GPIO_Label=TIM3_CH4_Y-
PB1.Signal=S_TIM3_CH4
PB10.GPIOParameters=GPIO_Label
PB10.GPIO_Label=LED_White
PB10.Signal=GPIO_Output
PB11.GPIOParameters=GPIO_Label
PB11.GPIO_Label=TIM2_CH4_EDF
PB11.Signal=S_TIM2_CH4
PB2.GPIOParameters=GPIO_Label
PB2.GPIO_Label=LED_Red
PB2.Signal=GPIO_Output
PB3.Mode=Trace_Asynchronous_SW
PB3.Signal=SYS_JTDO-SWO
PB4.GPIOParameters=GPIO_Label
PB4.GPIO_Label=CS_RF2
PB4.Signal=GPIO_Output
PB5.GPIOParameters=GPIO_Label
PB5.GPIO_Label=EN_RF2
PB5.Signal=GPIO_Output
PB7.GPIOParameters=GPIO_Label,GPIO_ModeDefaultEXTI
PB7.GPIO_Label=RF_IRQ1
PB7.GPIO_ModeDefaultEXTI=GPIO_MODE_IT_RISING
PB7.Signal=GPXTI7
PB8.GPIOParameters=GPIO_Label
PB8.GPIO_Label=EN_RF1
PB8.Signal=GPIO_Output
PB9.GPIOParameters=GPIO_Label
PB9.GPIO_Label=CS_RF1
PB9.Signal=GPIO_Output
PC10.GPIOParameters=GPIO_Label
PC10.GPIO_Label=UART4_TX_GPS
PC10.Mode=Asynchronous
PC10.Signal=UART4_TX
PC11.GPIOParameters=GPIO_Label
PC11.GPIO_Label=UART4_RX_GPS
PC11.Mode=Asynchronous
PC11.Signal=UART4_RX
PC4.GPIOParameters=GPIO_Label
PC4.GPIO_Label=CS_Ext
PC4.Signal=GPIO_Output
PC5.GPIOParameters=GPIO_Label
PC5.GPIO_Label=CS_SD
PC5.Signal=GPIO_Output
PC6.GPIOParameters=GPIO_Label
PC6.GPIO_Label=TIM3_CH1_X-
PC6.Signal=S_TIM3_CH1
PC7.GPIOParameters=GPIO_Label
PC7.GPIO_Label=TIM3_CH2_X+
PC7.Signal=S_TIM3_CH2
PC9.Mode=I2C
PC9.Signal=I2C3_SDA
PD2.GPIOParameters=GPIO_Label
PD2.GPIO_Label=RF_IRQ2
PD2.Signal=GPXTI2
PH0-OSC_IN.Mode=HSE-External-Oscillator
PH0-OSC_IN.Signal=RCC_OSC_IN
PH1-OSC_OUT.Mode=HSE-External-Oscillator
PH1-OSC_OUT.Signal=RCC_OSC_OUT
RCC.HSE_VALUE=25000000
RCC.SYSCLKFreq_VALUE=120000000
RCC.SYSCLKSource=RCC_SYSCLKSOURCE_PLLCLK
board=custom

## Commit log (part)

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2025-08-30 First commit
    separated Amon lander project, PCB+SW only
2025-08-30 Update
    readme
2025-11-04 docker and ozone
2026-01-17 Update
    A lot of code changes, radio driver implementation, basic decoding implementetion, state machine changed
2026-01-24 Update
    connection with link, stream data mode
2026-01-24 Update
    connection with link, stream data
2026-01-28 Update
    data stream optimization
2026-02-02 Update
    corected complementary filter, optimized telemetry send from 5 to 50Hz, start of Kalman filter development
2026-03-06 Update
    Implementation of logging - LittleFS, 50Hz, external flash
2026-03-07 Update
    Implementation of serial connection to drone, state change over radio (arm, flight start, flight stop...)
2026-03-08 Update
    functional logging (arm, flying, landed) and log dump over uart on gps port
2026-03-11 Update
    GNSS implemented, logging (flash) and radio works on the same bus - switching between SPI bus speed
2026-03-18 Update
    new flight controller development started (v3)
2026-03-30 Update
    compas driver - untested
2026-04-05 Update
    added first flight path buffer
2026-05-14 Update: development of new PCB_v3
2026-05-16 Update: finished routing of PCB_v3
2026-05-17 Update: finished PCB v3, gerbers, ordered board, readme update
2026-05-21 Update: code ported from stm32f4 to stm32h7 - untested
2026-05-23 Update: acados nmpc implementation started, readme upodate
2026-05-25 Update: first acados nmpc implementation complete, all libraries added
2026-05-27 Update: PMW3901 gyro compensation and distance tracking, autopilot start
2026-05-31 Update: PCB bringup in progress, some modifications done, fw in development
2026-06-06 Update: full FW port to PCB_v3 with all SPI problems solved, corrected timers, untested on craft
2026-06-07 Update: autopilot update - path planning used for nmpc reference, commands timeout
2026-06-08 Update: working and correctly mapped compas to drone body
2026-06-19 Update: working nmpc, needs tuning
2026-06-30 Update: first flight (with a lot of help but baseline works)!
